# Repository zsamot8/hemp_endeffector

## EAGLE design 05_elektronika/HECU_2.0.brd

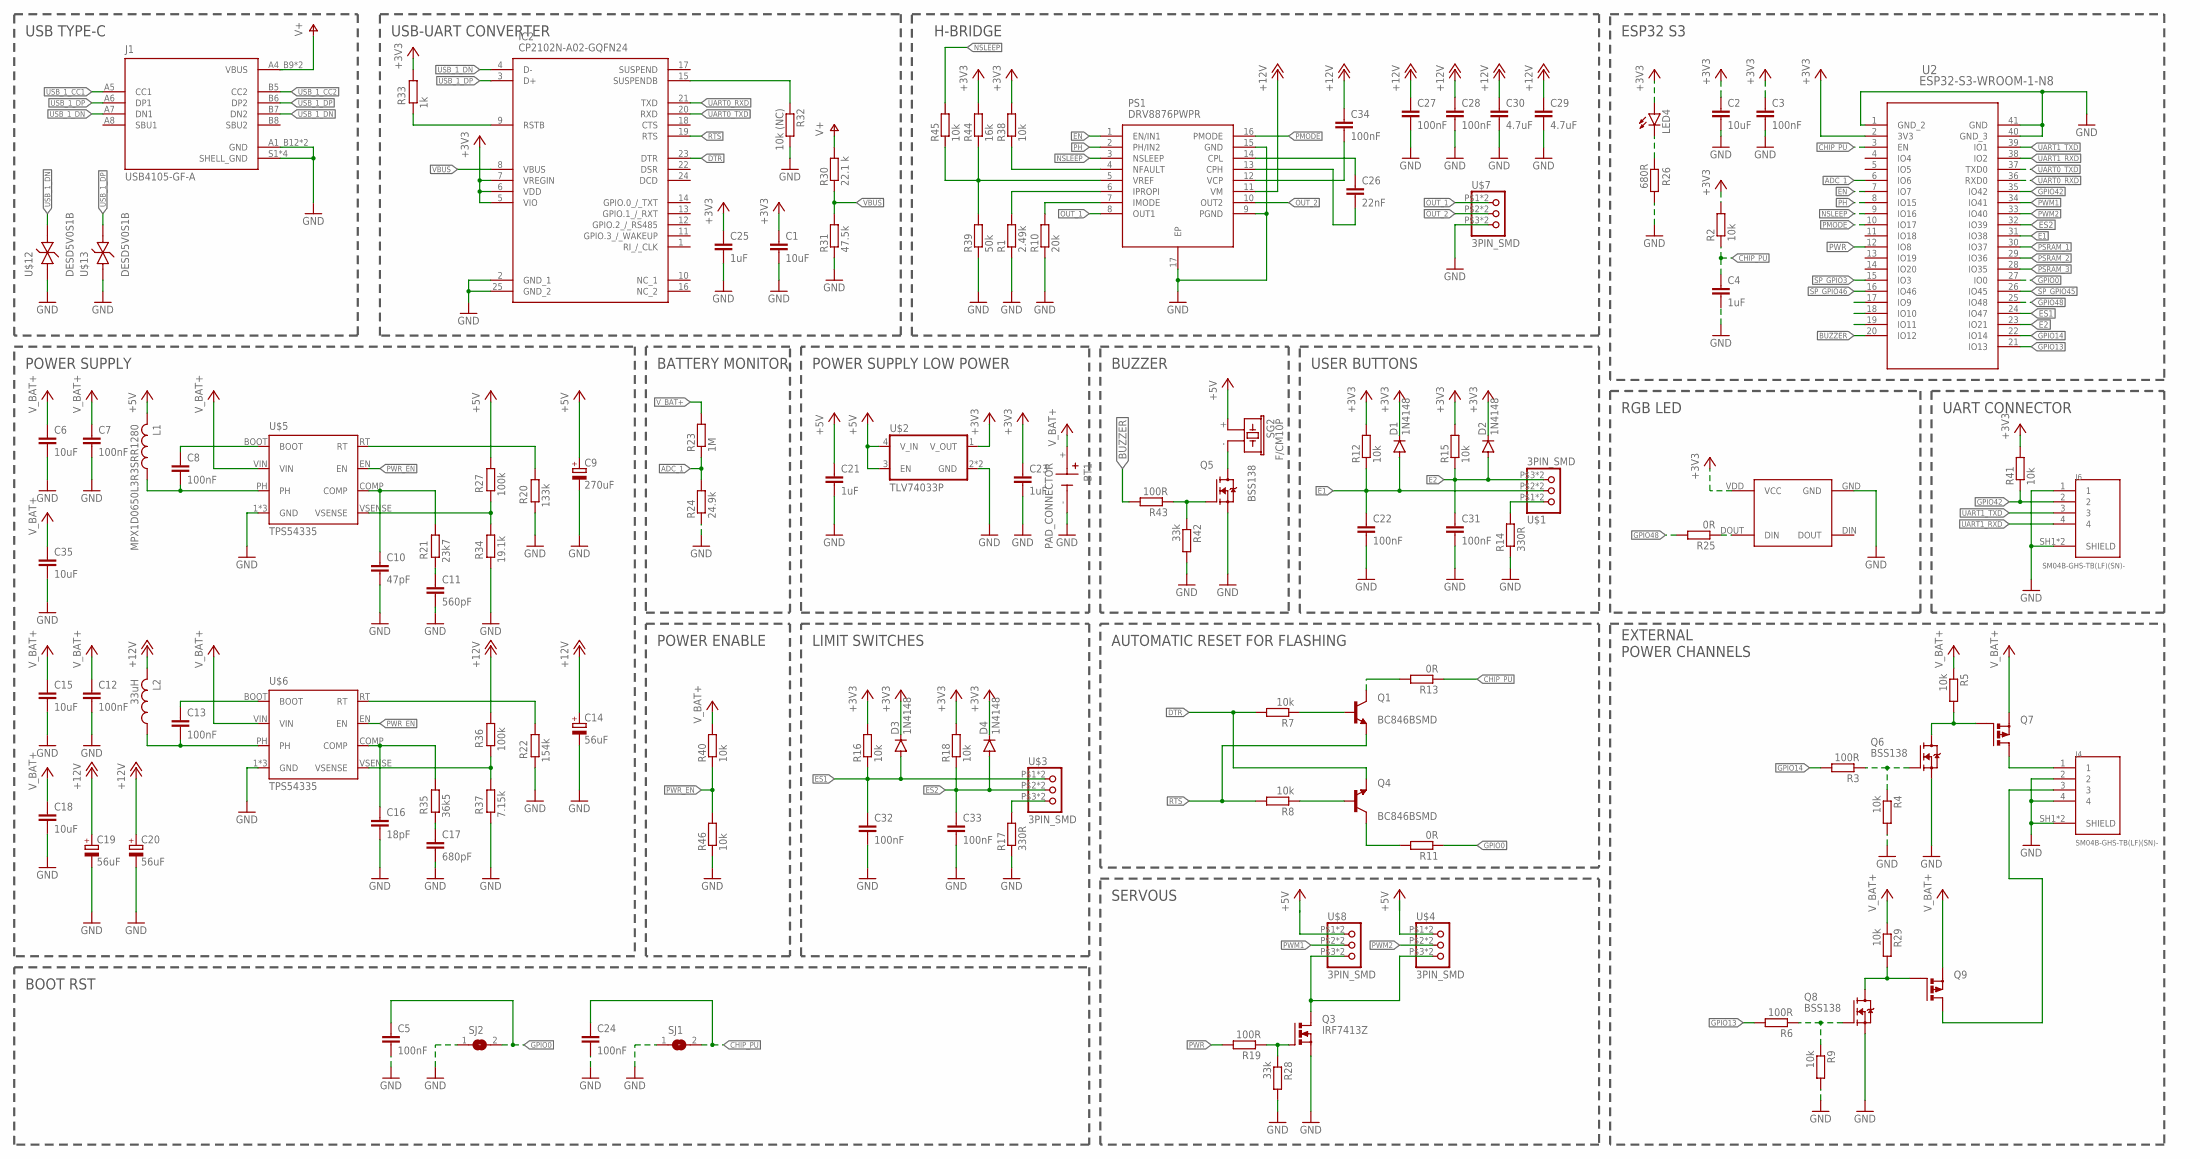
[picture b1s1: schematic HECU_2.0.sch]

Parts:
BT1: PAD_CONNECTOR; BAT_PADS
C1, C2, C6, C15, C18, C35: 10uF; C0805
C3, C5, C7, C8, C12, C13, C22, C24, C27, C28, C31, C32, C33, C34: 100nF; C0603
C4, C21, C23, C25: 1uF; C0603
C9: 270uF; PANASONIC_E
C10: 47pF; C0603
C11: 560pF; C0603
C14, C19, C20: 56uF; PANASONIC_C
C16: 18pF; C0603
C17: 680pF; C0603
C26: 22nF; C0603
C29, C30: 4.7uF; C0603
D1, D2, D3, D4: 1N4148; SOD80C
IC2: CP2102N-A02-GQFN24; QFN50P400X400X80-25N
J1: USB4105-GF-A; GCT_USB4105-GF-A
J4, J6: SM04B-GHS-TB(LF)(SN)-; JST_SM04B-GHS-TB(LF)(SN)-
L1: MPX1D0650L3R3SRR1280; COIL_SRR1280
L2: 33uH; COIL_MSS1210
LED4: LEDCHIPLED_0805; CHIPLED_0805
PS1: DRV8876PWPR; SOP65P640X120-17N
Q1, Q4: BC846BSMD; SOT23
Q3: IRF7413Z; SO-08
Q5, Q6, Q8: BSS138; SOT23
Q7, Q9: P-MOSFET-SO8; SO-08
R1: 2.49k; R0603
R2, R4, R5, R7, R8, R9, R12, R15, R16, R18, R29, R38, R40, R41, R45, R46: 10k; R0603
R3, R6, R19, R43: 100R; R0603
R10: 20k; R0603
R11, R13, R25: 0R; R0603
R14, R17: 330R; R0603
R20: 133k; R0603
R21: 23k7; R0603
R22: 154k; R0603
R23: 1M; R0603
R24: 24.9k; R0603
R26: 680R; R0603
R27, R36: 100k; R0603
R28, R42: 33k; R0603
R30: 22.1 k; R0603
R31: 47.5k; R0603
R32: 10k (NC); R0603
R33: 1k; R0603
R34: 19.1k; R0603
R35: 36k5; R0603
R37: 7.15k; R0603
R39: 50k; R0603
R44: 16k; R0603
RGB1: SK6812MINI; 2020REVMNT
SG2: F/CM10P
SJ1, SJ2: SJ
U2: ESP32-S3-WROOM-1-N8; ESP32-S3-WROOM-1-N8_EXP
U$1, U$3, U$4, U$7, U$8: 3PIN_SMD; 3PIN_PAD
U$2: TLV74033P; SUP_TPS3831L30DQNR
U$5, U$6: TPS54335; DDA0008E_L
U$12, U$13: DESD5V0S1B; DIO_BAS316_RRG

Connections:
+3V3: C1.1, C2.1, C3.1, C23.1, C25.1, D1.C, D2.C, D3.C, D4.C, IC2.5 (VIO), IC2.6 (VDD), IC2.7 (VREGIN), LED4.A, R2.2, R12.2, R15.2, R16.2, R18.2, R33.1, R38.2, R41.2, R44.2, RGB1.VDD (VCC), U2.2 (3V3), U$2.1 (V_OUT)
+5V: C9.+, C21.1, L1.2, R27.1, SG2.+ (1), U$2.3 (EN), U$2.4 (V_IN), U$4.P$1 (1), U$4.P$4 (1), U$8.P$1 (1), U$8.P$4 (1)
+12V: C14.+, C19.+, C20.+, C27.1, C28.1, C29.1, C30.1, C34.1, L2.2, PS1.11 (VM), R36.1
ADC_1: R23.1, R24.2, U2.6 (IO6)
BUZZER: R43.2, U2.20 (IO12)
CHIP_PU: C4.1, C24.1, R2.1, R13.1, SJ1.2, U2.3 (EN)
DTR: IC2.23 (DTR), Q4.2 (E), R7.2
E1: C22.1, D1.A, R12.1, U2.31 (IO38), U$1.P$2 (2), U$1.P$5 (2)
E2: C31.1, D2.A, R15.1, U2.23 (IO21), U$1.P$3 (3), U$1.P$6 (3)
EN: PS1.1 (EN/IN1), U2.7 (IO7)
ES1: C32.1, D3.A, R16.1, U2.24 (IO47), U$3.P$1 (1), U$3.P$4 (1)
ES2: C33.1, D4.A, R18.1, U2.32 (IO39), U$3.P$2 (2), U$3.P$5 (2)
GND: BT1.-, C1.2, C2.2, C3.2, C4.2, C5.2, C6.2, C7.2, C9.-, C10.2, C11.2, C12.2, C14.-, C15.2, C16.2, C17.2, C18.2, C19.-, C20.-, C21.2, C22.2, C23.2, C24.2, C25.2, C27.2, C28.2, C29.2, C30.2, C31.2, C32.2, C33.2, C35.2, IC2.2 (GND_1), IC2.25 (GND_2), J1.A1_B12 (GND), J1.B1_A12 (GND), J1.S1 (SHELL_GND), J1.S2 (SHELL_GND), J1.S3 (SHELL_GND), J1.S4 (SHELL_GND), J4.2, J4.4, J4.SH1 (SHIELD), J4.SH2 (SHIELD), J6.1, J6.SH1 (SHIELD), J6.SH2 (SHIELD), PS1.9 (PGND), PS1.15 (GND), PS1.17 (EP), Q3.1 (S), Q3.2 (S), Q3.3 (S), Q5.2 (S), Q6.2 (S), Q8.2 (S), R1.1, R4.2, R9.2, R10.1, R14.1, R17.1, R20.2, R22.2, R24.1, R26.1, R28.2, R31.1, R32.2, R34.2, R37.2, R39.1, R42.2, R46.1, RGB1.GND, SJ1.1, SJ2.1, U2.1 (GND_2), U2.40 (GND_3), U2.41 (GND), U$2.2 (GND), U$2.5 (GND), U$5.1 (GND), U$5.9 (GND), U$5.GND, U$6.1 (GND), U$6.9 (GND), U$6.GND, U$7.P$3 (3), U$7.P$6 (3), U$12.A (1), U$13.A (1)
GPIO0: C5.1, R11.1, SJ2.2, U2.27 (IO0)
GPIO13: R6.2, U2.21 (IO13)
GPIO14: R3.2, U2.22 (IO14)
GPIO42: J6.2, R41.1, U2.35 (IO42)
GPIO48: R25.2, U2.25 (IO48)
unnamed: R17.2, U$3.P$3 (3), U$3.P$6 (3)
unnamed: R14.2, U$1.P$1 (1), U$1.P$4 (1)
unnamed: J4.1, Q7.5 (D), Q7.6 (D), Q7.7 (D), Q7.8 (D)
unnamed: Q1.3 (C), R13.2
unnamed: Q6.1 (G), R3.1, R4.1
unnamed: Q4.3 (C), R11.2
unnamed: R20.1, U$5.RT
unnamed: C10.1, R21.1, U$5.COMP
unnamed: C8.1, U$5.BOOT
unnamed: Q4.1 (B), R8.1
unnamed: Q5.3 (D), SG2.- (2)
unnamed: Q1.1 (B), R7.1
unnamed: IC2.15 (SUSPENDB), R32.1
unnamed: Q6.3 (D), Q7.4 (G), R5.2
unnamed: Q3.5 (D), Q3.6 (D), Q3.7 (D), Q3.8 (D), U$4.P$3 (3), U$4.P$6 (3), U$8.P$3 (3), U$8.P$6 (3)
unnamed: R25.1, RGB1.DOUT (DIN)
unnamed: LED4.C, R26.2
unnamed: Q8.1 (G), R6.1, R9.1
unnamed: Q8.3 (D), Q9.4 (G), R29.2
unnamed: Q5.1 (G), R42.1, R43.1
unnamed: C8.2, L1.1, U$5.PH
unnamed: IC2.9 (RSTB), R33.2
unnamed: R27.2, R34.1, U$5.VSENSE
unnamed: C11.1, R21.2
unnamed: R22.1, U$6.RT
unnamed: C16.1, R35.1, U$6.COMP
unnamed: C13.1, U$6.BOOT
unnamed: C13.2, L2.1, U$6.PH
unnamed: J4.3, Q9.5 (D), Q9.6 (D), Q9.7 (D), Q9.8 (D)
unnamed: R36.2, R37.1, U$6.VSENSE
unnamed: Q3.4 (G), R19.1, R28.1
unnamed: C17.1, R35.2
unnamed: C34.2, PS1.12 (VCP)
unnamed: C26.1, PS1.14 (CPL)
unnamed: C26.2, PS1.13 (CPH)
unnamed: PS1.6 (IPROPI), R1.2
unnamed: PS1.7 (IMODE), R10.2
unnamed: PS1.4 (NFAULT), R38.1
unnamed: PS1.5 (VREF), R39.2, R44.1, R45.1
NSLEEP: PS1.3 (NSLEEP), R45.2, U2.9 (IO16)
OUT_1: PS1.8 (OUT1), U$7.P$1 (1), U$7.P$4 (1)
OUT_2: PS1.10 (OUT2), U$7.P$2 (2), U$7.P$5 (2)
PD_INT: U2.17 (IO9)
PD_SCL: U2.19 (IO11)
PD_SDA: U2.18 (IO10)
PH: PS1.2 (PH/IN2), U2.8 (IO15)
PMODE: PS1.16 (PMODE), U2.10 (IO17)
PSRAM_1: U2.30 (IO37)
PSRAM_2: U2.29 (IO36)
PSRAM_3: U2.28 (IO35)
PWM1: U2.34 (IO41), U$8.P$2 (2), U$8.P$5 (2)
PWM2: U2.33 (IO40), U$4.P$2 (2), U$4.P$5 (2)
PWR: R19.2, U2.12 (IO8)
PWR_EN: R40.1, R46.2, U$5.EN, U$6.EN
RTS: IC2.19 (RTS), Q1.2 (E), R8.2
SP_GPIO3: U2.15 (IO3)
SP_GPIO45: U2.26 (IO45)
SP_GPIO46: U2.16 (IO46)
UART0_RXD: IC2.21 (TXD), U2.36 (RXD0)
UART0_TXD: IC2.20 (RXD), U2.37 (TXD0)
UART1_RXD: J6.4, U2.38 (IO2)
UART1_TXD: J6.3, U2.39 (IO1)
USB_1_CC1: J1.A5 (CC1)
USB_1_CC2: J1.B5 (CC2)
USB_1_DN: IC2.4 (D-), J1.A7 (DN1), J1.B7 (DN2), U$12.C (2)
USB_1_DP: IC2.3 (D+), J1.A6 (DP1), J1.B6 (DP2), U$13.C (2)
V+: J1.A4_B9 (VBUS), J1.B4_A9 (VBUS), R30.2
VBUS: IC2.8 (VBUS), R30.1, R31.2
V_BAT+: BT1.+, C6.1, C7.1, C12.1, C15.1, C18.1, C35.1, Q7.1 (S), Q7.2 (S), Q7.3 (S), Q9.1 (S), Q9.2 (S), Q9.3 (S), R5.1, R23.2, R29.1, R40.2, U$5.VIN, U$6.VIN

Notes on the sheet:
BATTERY MONITOR
USB TYPE-C
USB-UART CONVERTER
POWER ENABLE
LIMIT SWITCHES
SERVOUS
BUZZER
USER BUTTONS
AUTOMATIC RESET FOR FLASHING
RGB LED
ESP32 S3
BOOT RST
UART CONNECTOR
EXTERNAL POWER CHANNELS
POWER SUPPLY
POWER SUPPLY LOW POWER
H-BRIDGE

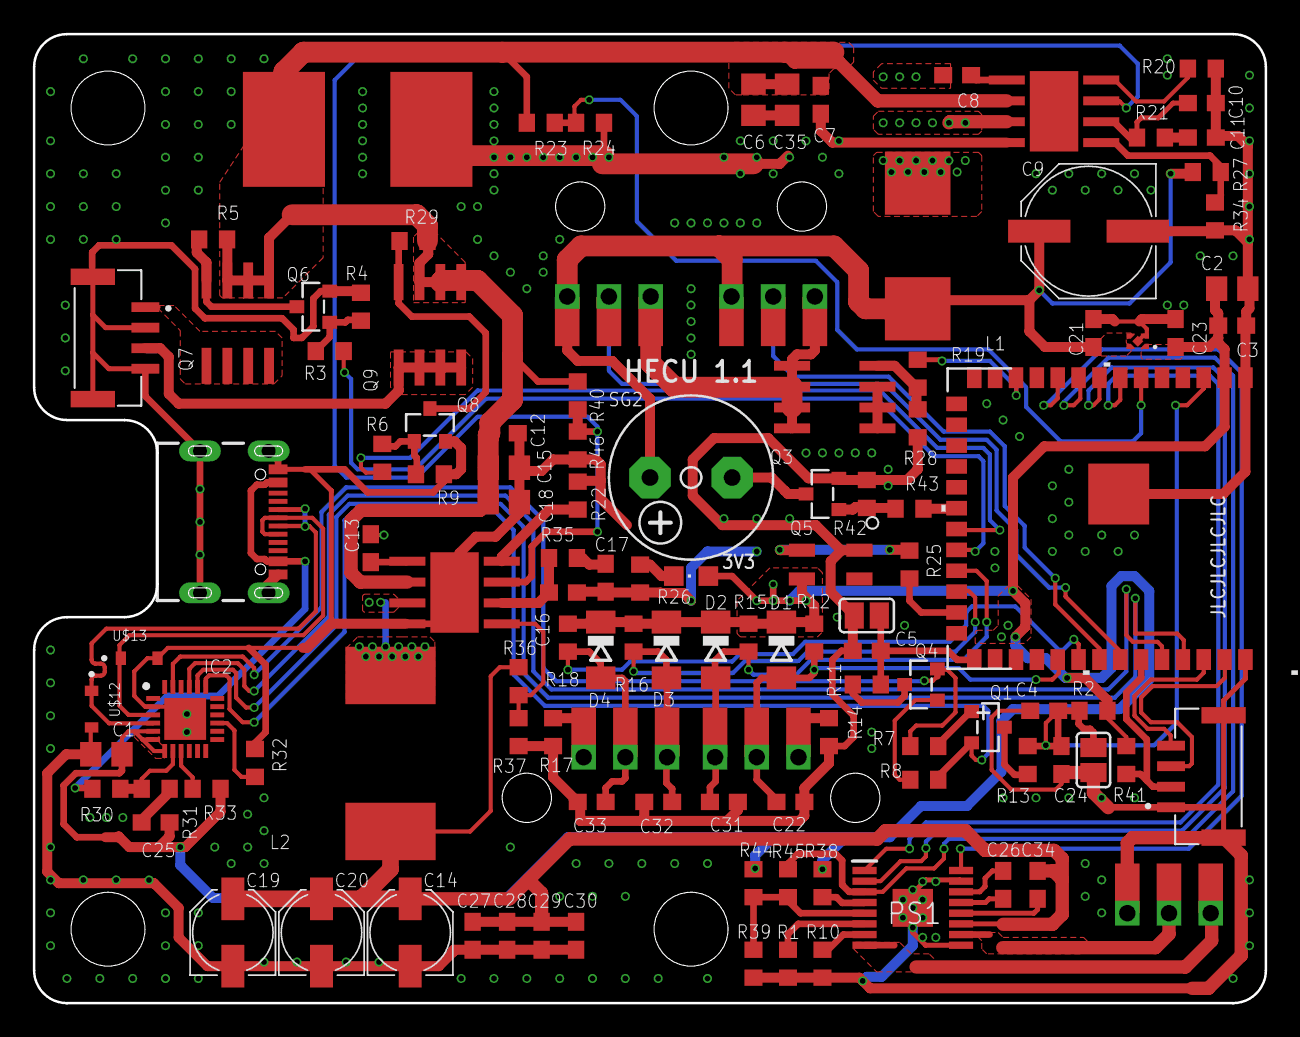
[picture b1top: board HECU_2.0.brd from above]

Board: 2 copper layers, 75.0 x 59.0 mm, 117 parts (0 on the bottom side), 76 nets.

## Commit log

2022-09-05 Git init
2022-09-23 CAD model added

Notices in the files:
parts and their libraries:
COPYRIGHT: Copyright (C) 2022 Ultra Librarian. All rights reserved.
